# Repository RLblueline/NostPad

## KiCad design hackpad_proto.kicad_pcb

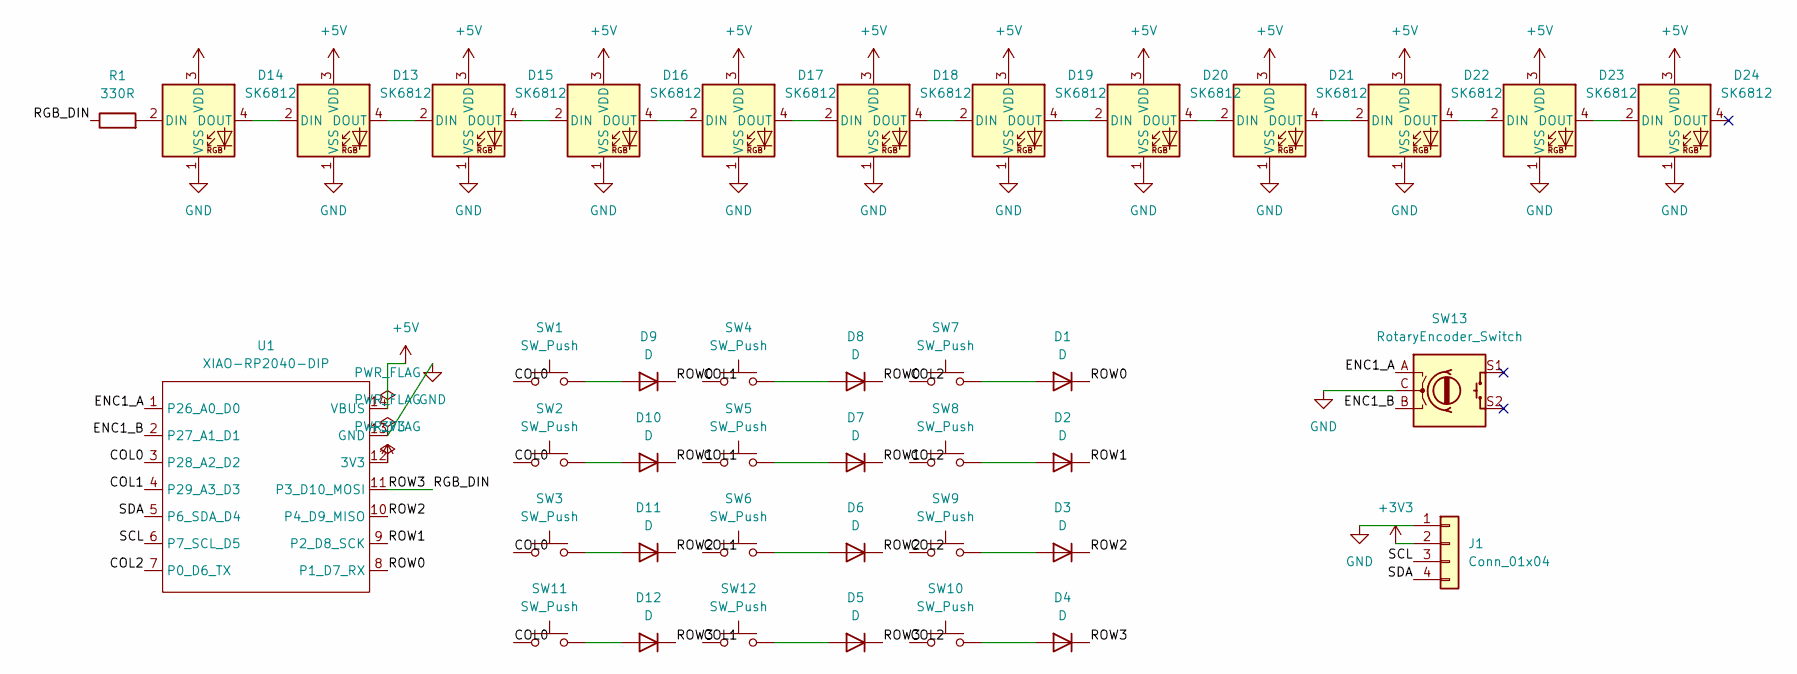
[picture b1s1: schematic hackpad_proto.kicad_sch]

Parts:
D1, D2, D3, D4, D5, D6, D7, D8, D9, D10, D11, D12: D; D_DO-35_SOD27_P7.62mm_Horizontal
D13, D14, D15, D16, D17, D18, D19, D20, D21, D22, D23, D24: SK6812; SK6812MINI-E_fixed
J1: Conn_01x04; PinHeader_1x04_P2.54mm_Vertical
R1: 330R; R_0402_1005Metric
SW1, SW2, SW3, SW4, SW5, SW6, SW7, SW8, SW9, SW10, SW11, SW12: SW_Push; SW_Cherry_MX_1.00u_PCB
SW13: RotaryEncoder_Switch; RotaryEncoder_Alps_EC11E-Switch_Vertical_H20mm
U1: XIAO-RP2040-DIP; XIAO-Generic-Hybrid-14P-2.54-21X17.8MM

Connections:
+3V3: J1.2, U1.12 (3V3)
+5V: D13.3 (VDD), D14.3 (VDD), D15.3 (VDD), D16.3 (VDD), D17.3 (VDD), D18.3 (VDD), D19.3 (VDD), D20.3 (VDD), D21.3 (VDD), D22.3 (VDD), D23.3 (VDD), D24.3 (VDD), U1.14 (VBUS)
/COL0: SW1.1, SW2.1, SW3.1, SW11.1, U1.3 (P28_A2_D2)
/COL1: SW4.1, SW5.1, SW6.1, SW12.1, U1.4 (P29_A3_D3)
/COL2: SW7.1, SW8.1, SW9.1, SW10.1, U1.7 (P0_D6_TX)
/ENC1_A: SW13.A, U1.1 (P26_A0_D0)
/ENC1_B: SW13.B, U1.2 (P27_A1_D1)
/RGB_DIN: D4.1 (K), D5.1 (K), D12.1 (K), R1.1, U1.11 (P3_D10_MOSI)
/ROW0: D1.1 (K), D8.1 (K), D9.1 (K), U1.8 (P1_D7_RX)
/ROW1: D2.1 (K), D7.1 (K), D10.1 (K), U1.9 (P2_D8_SCK)
/ROW2: D3.1 (K), D6.1 (K), D11.1 (K), U1.10 (P4_D9_MISO)
/SCL: J1.3, U1.6 (P7_SCL_D5)
/SDA: J1.4, U1.5 (P6_SDA_D4)
GND: D13.1 (VSS), D14.1 (VSS), D15.1 (VSS), D16.1 (VSS), D17.1 (VSS), D18.1 (VSS), D19.1 (VSS), D20.1 (VSS), D21.1 (VSS), D22.1 (VSS), D23.1 (VSS), D24.1 (VSS), J1.1, SW13.C, U1.13 (GND)
unnamed: D1.2 (A), SW7.2
unnamed: D2.2 (A), SW8.2
unnamed: D3.2 (A), SW9.2
unnamed: D4.2 (A), SW10.2
unnamed: D5.2 (A), SW12.2
unnamed: D6.2 (A), SW6.2
unnamed: D7.2 (A), SW5.2
unnamed: D8.2 (A), SW4.2
unnamed: D9.2 (A), SW1.2
unnamed: D10.2 (A), SW2.2
unnamed: D11.2 (A), SW3.2
unnamed: D12.2 (A), SW11.2
unnamed: D13.2 (DIN), D14.4 (DOUT)
unnamed: D13.4 (DOUT), D15.2 (DIN)
unnamed: D14.2 (DIN), R1.2
unnamed: D15.4 (DOUT), D16.2 (DIN)
unnamed: D16.4 (DOUT), D17.2 (DIN)
unnamed: D17.4 (DOUT), D18.2 (DIN)
unnamed: D18.4 (DOUT), D19.2 (DIN)
unnamed: D19.4 (DOUT), D20.2 (DIN)
unnamed: D20.4 (DOUT), D21.2 (DIN)
unnamed: D21.4 (DOUT), D22.2 (DIN)
unnamed: D22.4 (DOUT), D23.2 (DIN)
unnamed: D23.4 (DOUT), D24.2 (DIN)

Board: 2 copper layers, 40 parts (0 on the bottom side), 38 nets, no tracks yet.

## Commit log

2026-06-13 Force clean repository structure
2026-06-14 Updated NostPad hardware design layout
